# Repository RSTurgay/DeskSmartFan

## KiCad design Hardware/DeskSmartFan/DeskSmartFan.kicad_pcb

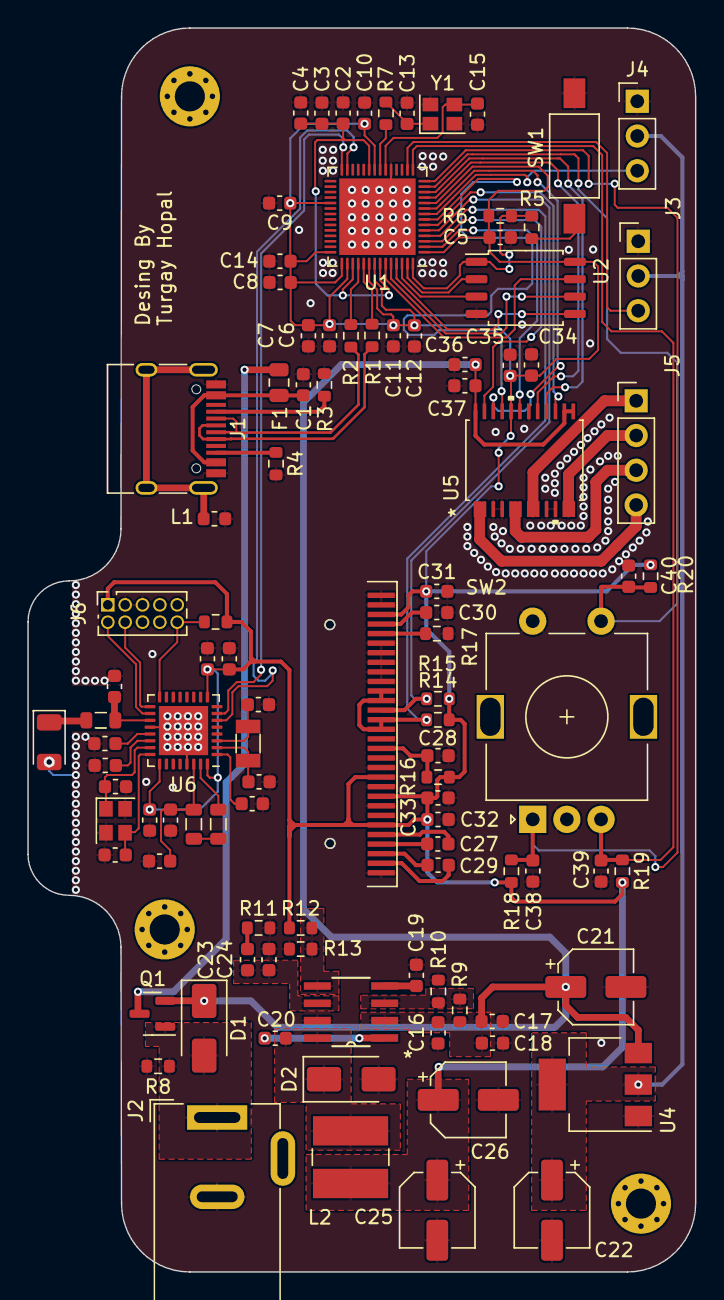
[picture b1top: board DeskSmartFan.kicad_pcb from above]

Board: 2 copper layers, 48.8 x 91.0 mm, 102 parts (0 on the bottom side), 74 nets.

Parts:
AE1: Antenna_Chip; Johanson_2450AT18x100
C1, C4, C6, C27, C29, C31, C47: 1uF; C_0603_1608Metric
C2, C3, C5, C7, C8, C9, C10, C11, C12, C14, C28, C32, C35, C36, C38, C39, C40, C50, C51, C52: 100nF; C_0603_1608Metric
C13, C15: 22pF; C_0603_1608Metric
C16, C17, C53: 4.7uF; C_0603_1608Metric
C18, C19: 10nF; C_0603_1608Metric
C20, C23: 1nF; C_0603_1608Metric
C21, C22, C25, C26: 47uF; CP_Elec_5x4.4
C24: 47pF; C_0603_1608Metric
C30, C33: 2.2uF; C_0603_1608Metric
C34, C37: 10uF; C_0603_1608Metric
C41, C42, C43, C44: 12pF; C_0603_1608Metric
C45: 0.8pF; C_0603_1608Metric
C46, C49: N.C; C_0603_1608Metric
C48: 100pF; C_0603_1608Metric
D1: D; D_SMA
D2: B340; D_SMA
DS1: OLED-128O064D
F1: 6V/1.5A; Fuse_0805_2012Metric
J1: USB_C_Receptacle_USB2.0; USB_C_Receptacle_HRO_TYPE-C-31-M-12
J2: Barrel_Jack; BarrelJack_Wuerth_6941xx301002
J3, J4: Conn_01x03_Pin; PinHeader_1x03_P2.54mm_Vertical
J5: PinHeader_1x04_P2.54mm_Vertical
J6: NRF_Debug; PinSocket_2x05_P1.27mm_Vertical
L1: 220R; L_0603_1608Metric
L2: 6.8uH; L_TracoPower_TCK-047_5.2x5.8mm
L3: 3.9nH; L_0805_2012Metric
L4: 10uH; L_0805_2012Metric
L5: 15nH; L_0805_2012Metric
Q1: IRLML5203; SOT-23
R1, R2: 47R; R_0603_1608Metric
R3, R4: 5.1K; R_0603_1608Metric
R5, R7: 1K; R_0603_1608Metric
R6: DNF; R_0603_1608Metric
R8, R10: 100K; R_0603_1608Metric
R9: 150K; R_0603_1608Metric
R11: 29.4K; R_0603_1608Metric
R12: 10.2K; R_0603_1608Metric
R13: 3.24K; R_0603_1608Metric
R14, R15, R16: 4.7K; R_0603_1608Metric
R17: 390K; R_0603_1608Metric
R18, R19, R20, R21: 10K; R_0603_1608Metric
SW1: BOOT; SW_SPST_FSMSM
SW2: RotaryEncoder_Switch; RotaryEncoder_Alps_EC11E-Switch_Vertical_H20mm
U1: RP2040; QFN-56-1EP_7x7mm_P0.4mm_EP5.6x5.6mm
U2: W25Q128JVS; SOIC-8_5.23x5.23mm_P1.27mm
U3: TPS54331DR; D8
U4: AMS1117-5.0; SOT-223-3_TabPin2
U5: TB6612FNG_C_8_EL
U6: nRF52811-QCxx; QFN-32-1EP_5x5mm_P0.5mm_EP3.6x3.6mm
Y1: 12MHz; Crystal_SMD_2520-4Pin_2.5x2.0mm
Y2: Crystal_GND24_Small; Crystal_SMD_2520-4Pin_2.5x2.0mm
Y3: 32.768kHz; Crystal_SMD_3215-2Pin_3.2x1.5mm

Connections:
+1V1: C2.1, C3.1, C4.1, U1.23 (DVDD), U1.45 (VREG_VOUT), U1.50 (DVDD)
+3V3: C5.1, C6.1, C7.1, C8.1, C9.1, C10.1, C11.1, C12.1, C14.1, C25.1, C26.1, C31.1, C32.1, C33.1, C34.1, C35.1, C51.1, C52.1, C53.1, DS1.6 (VBAT), DS1.9 (VDD), DS1.11 (BS1), DS1.28 (VCC), J6.1, L2.2, R6.2, R12.1, R14.1, R15.1, R16.1, R18.2, R19.2, R20.1, R21.1, U1.1 (IOVDD), U1.10 (IOVDD), U1.22 (IOVDD), U1.33 (IOVDD), U1.42 (IOVDD), U1.43 (ADC_AVDD), U1.44 (VREG_IN), U1.48 (USB_VDD), U1.49 (IOVDD), U2.8 (VCC), U5.20 (VCC), U6.9 (VDD), U6.25 (VDD), U6.32 (VDD)
+5V: C22.1, J3.2, J4.2, U4.2 (VO)
+12V: D1.2 (A), J2.1, Q1.1 (G), R8.2
/Fan Control/AIN1: U1.7 (GPIO5), U5.21 (AIN1)
/Fan Control/AIN2: U1.9 (GPIO7), U5.22 (AIN2)
/Fan Control/BIN1: U1.11 (GPIO8), U5.17 (BIN1)
/Fan Control/BIN2: U1.12 (GPIO9), U5.16 (BIN2)
/Fan Control/ENGINE_A_1: J5.4, U5.1 (AO1), U5.2 (AO1)
/Fan Control/ENGINE_A_2: J5.3, U5.5 (AO2), U5.6 (AO2)
/Fan Control/ENGINE_B_1: J5.2, U5.11 (BO1), U5.12 (BO1)
/Fan Control/ENGINE_B_2: J5.1, U5.7 (BO2), U5.8 (BO2)
/Fan Control/PWMA: U1.3 (GPIO1), U5.23 (PWMA)
/Fan Control/PWMB: U1.6 (GPIO4), U5.15 (PWMB)
/Fan Control/STBY: U1.2 (GPIO0), U5.19 (STBY)
/Fan Control/VIN: C16.1, C17.1, C18.1, C21.1, C36.1, C37.1, D1.1 (K), Q1.2 (S), R9.1, U3.2 (VIN), U4.3 (VI), U5.13 (VM2), U5.14 (VM3), U5.24 (VM1)
/NRF52811/DEC4: C46.2, C47.2, L5.2, U6.30 (DEC4)
/NRF52811/NRESET: J6.10, R21.2, U6.16 (P0.21/~RESET)
/NRF52811/P0.06: U1.27 (GPIO16), U6.6 (P0.06)
/NRF52811/P0.09: U1.28 (GPIO17), U6.7 (P0.09)
/NRF52811/SWDCLK: J6.4, U6.17 (SWDCLK)
/NRF52811/SWDIO: J6.2, U6.18 (SWDIO)
/NRF52811/XC1: C41.1, U6.23 (XC1), Y2.1
/NRF52811/XC2: C42.1, U6.24 (XC2), Y2.3
/NRF52811/XL1: C43.1, U6.2 (XL1/P0.00), Y3.1
/NRF52811/XL2: C44.1, U6.3 (XL2/P0.01), Y3.2
/Power Control/BOOT: C20.1, D2.1 (K), L2.1, U3.8 (PH)
/Power Control/VSENSE: R12.2, R13.1, U3.5 (VSENSE)
/RP2040/GPIO2: DS1.16 (R/~W), DS1.17 (E/~RD), DS1.19 (D1), DS1.20 (D2), R14.2, U1.4 (GPIO2)
/RP2040/GPIO3: DS1.18 (D0), R15.2, U1.5 (GPIO3)
/RP2040/GPIO6: J4.3, U1.8 (GPIO6)
/RP2040/GPIO10: C40.2, R20.2, SW2.S1, U1.13 (GPIO10)
/RP2040/GPIO11: C38.2, R18.1, SW2.A, U1.14 (GPIO11)
/RP2040/GPIO12: C39.1, R19.1, SW2.B, U1.15 (GPIO12)
/RP2040/GPIO13: J3.3, U1.16 (GPIO13)
/RP2040/QSPI_SCLK: U1.52 (QSPI_SCLK), U2.6 (CLK)
/RP2040/QSPI_SD0: U1.53 (QSPI_SD0), U2.5 (DI(IO0))
/RP2040/QSPI_SD1: U1.55 (QSPI_SD1), U2.2 (DO(IO1))
/RP2040/QSPI_SD2: U1.54 (QSPI_SD2), U2.3 (IO2)
/RP2040/QSPI_SD3: U1.51 (QSPI_SD3), U2.7 (IO3)
/RP2040/QSPI_SS: R5.2, R6.1, U1.56 (QSPI_SS), U2.1 (~CS)
/RP2040/USB_D+: J1.A6 (D+), J1.B6 (D+), R1.1
/RP2040/USB_D-: J1.A7 (D-), J1.B7 (D-), R2.1
/RP2040/USB_DM: R2.2, U1.46 (USB_DM)
/RP2040/USB_DP: R1.2, U1.47 (USB_DP)
/RP2040/XIN: C15.1, U1.20 (XIN), Y1.3
/RP2040/XOUT: R7.2, U1.21 (XOUT)
GND: AE1.2 (PCB_Trace), C1.1, C2.2, C3.2, C4.2, C5.2, C6.2, C7.2, C8.2, C9.2, C10.2, C11.2, C12.2, C13.2, C14.2, C15.2, C16.2, C17.2, C18.2, C19.2, C21.2, C22.2, C24.2, C25.2, C26.2, C28.2, C30.1, C31.2, C32.2, C33.2, C34.2, C35.2, C36.2, C37.2, C38.1, C39.2, C40.1, C41.2, C42.2, C43.2, C44.2, C45.1, C46.1, C47.1, C48.1, C49.1, C50.1, C51.2, C52.2, C53.2, D2.2 (A), DS1.1 (GND), DS1.8 (VSS), DS1.10 (BS0), DS1.12 (BS2), DS1.21 (D3), DS1.22 (D4), DS1.23 (D5), DS1.24 (D6), DS1.25 (D7), DS1.29 (VLSS), DS1.30 (GND), J1.A1 (GND), J1.A12 (GND), J1.B1 (GND), J1.B12 (GND), J2.2, J3.1, J4.1, J6.3, J6.5, L1.2, R3.2, R4.2, R8.1, R10.2, R11.2, R13.2, R17.1, SW1.1, SW2.C, SW2.S2, U1.19 (TESTEN), U1.57 (GND), U2.4 (GND), U3.7 (GND), U4.1 (GND), U5.3 (PGND1), U5.4 (PGND1), U5.9 (PGND2), U5.10 (PGND2), U5.18 (GND), U6.20 (VSS), U6.29 (VSS), U6.33 (VSS), Y1.2, Y1.4, Y2.2, Y2.4
unnamed: AE1.1 (FEED), L3.1
unnamed: C1.2, F1.1, J1.A4 (VBUS), J1.A9 (VBUS), J1.B4 (VBUS), J1.B9 (VBUS)
unnamed: C13.1, R7.1, Y1.1
unnamed: C23.2, R11.1
unnamed: C27.1, DS1.5 (C1N)
unnamed: C27.2, DS1.4 (C1P)
unnamed: C29.2, DS1.2 (C2N)
unnamed: C29.1, DS1.3 (C2P)
unnamed: DS1.26 (IREF), R17.2
unnamed: C30.2, DS1.27 (VCOMH)
unnamed: C28.1, DS1.14 (~RES), R16.2
unnamed: J1.A5 (CC1), R3.1
unnamed: J1.B5 (CC2), R4.1
unnamed: J1.S1 (SHIELD), L1.1
unnamed: L4.2, L5.1
unnamed: R5.1, SW1.2
unnamed: C20.2, U3.1 (BOOT)
unnamed: C23.1, C24.1, U3.6 (COMP)
unnamed: R9.2, R10.1, U3.3 (EN)
unnamed: C19.1, U3.4 (SS)
unnamed: C45.2, L3.2, U6.19 (ANT)
unnamed: L4.1, U6.31 (DCC)
unnamed: C50.2, U6.1 (DEC1)
unnamed: C49.2, U6.21 (DEC2)
unnamed: C48.2, U6.22 (DEC3)
VBUS: F1.2, Q1.3 (D)

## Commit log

2023-08-05 First Init
2023-08-05 First Init Update added Pico Project Structure

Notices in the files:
parts and their libraries:
Copyright 2021 Accelerated Designs. All rights reserved.
